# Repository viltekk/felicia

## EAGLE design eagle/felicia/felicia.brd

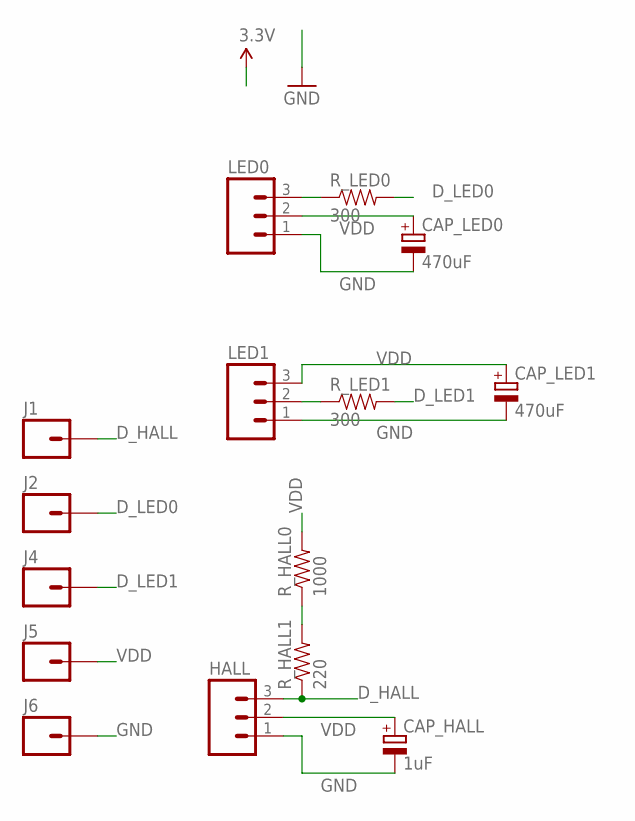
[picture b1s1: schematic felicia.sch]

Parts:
CAP_HALL: 1uF; E5-4
CAP_LED0, CAP_LED1: 470uF; E3,5-8
HALL: M031X03_NO_SILK; 1X03_NO_SILK
J1, J2, J4, J5, J6: M01NOSILK-KIT; 1X01NS-KIT
LED0, LED1: M031X03_NO_SILK; 1X03_NO_SILK
R_HALL0: 1000; AXIAL-0.4
R_HALL1: 220; AXIAL-0.4
R_LED0, R_LED1: 300; AXIAL-0.4

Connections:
D_HALL: HALL.3, J1.1, R_HALL1.P$1 (1)
D_LED0: J2.1, R_LED0.P$2 (2)
D_LED1: J4.1, R_LED1.P$2 (2)
GND: CAP_HALL.-, CAP_LED0.-, CAP_LED1.-, HALL.1, J6.1, LED0.1, LED1.1
unnamed: R_HALL0.P$1 (1), R_HALL1.P$2 (2)
unnamed: LED1.2, R_LED1.P$1 (1)
unnamed: LED0.3, R_LED0.P$1 (1)
VDD: CAP_HALL.+, CAP_LED0.+, CAP_LED1.+, HALL.2, J5.1, LED0.2, LED1.3, R_HALL0.P$2 (2)

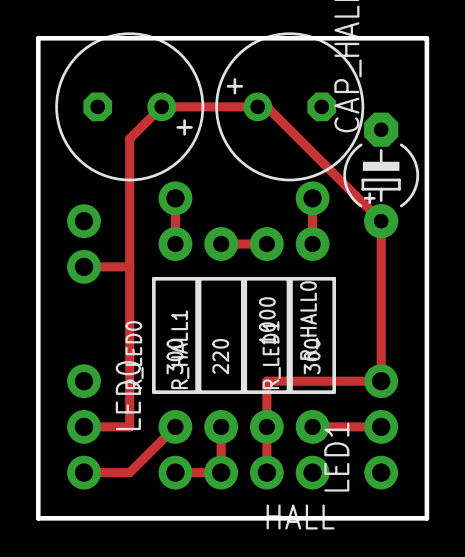
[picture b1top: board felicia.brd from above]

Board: 2 copper layers, 21.6 x 26.7 mm, 15 parts (0 on the bottom side), 8 nets.

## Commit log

2018-06-18 started working on cad model
2018-06-20 first try on upper body
2018-06-20 thickened some walls in the cad that were too thin for 3d printing
2018-06-26 trying out new model, previous wing was too small for LED
2018-06-29 some improvements to design
2018-07-01 trying out new design for wheel axel holder
2018-07-03 1.0 of cad
2018-07-06 initial arduino code
2018-07-06 removed debug prints and did some code cleanup
2018-07-29 new cad, new custom pcb and updated arduino code that works on the pro trinket

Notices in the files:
parts and their libraries:
SparkFun-Connectors: Licensing: Creative Commons ShareAlike 4.0 International - https://creativecommons.org/licenses/by-sa/4.0
